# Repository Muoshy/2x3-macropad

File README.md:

# 2x3 Macropad

Extremely simple 2x3 macropad with sandwich case.

  - QMK firmware
  - Acrylic sandwich case
  - Encoder support
  
## Schematic

## PCB

## Case

Case plates for laser cutting. 0.15 mm kerf already accounted for in .dxf files.
Choose one of the three switch plates according to your encoder placement. 
For same results as image above, engrave on 2 layer acrylic.

  - 4x M3 20mm screws
  - 4x M3 nuts

## Software
Running on QMK firmware. Use QMK Toolbox to flash with provided HEX file.
Then use VIA configurator to configure keybinds.
For further customization (encoder keycodes), setup a QMK build environment and compile your own HEX files.

## Flashing
  - Download and open QMK Toolbox
  - Select HEX file
  - Choose ATMega32u4 as microcontroller
  - Push reset button on board and then press flash button in toolbox.

## Keybinds
  - Download and install VIA Configurator
  - Open VIA and go to File->Import Keymap
  - Select the keymap.json file
  - Plug in the macropad

## BOM

| Component                		| Quantity 	| Link 								|
|--------------------------		|----------	|------								|
| MX switches              		| 6x (5x)   |      								|
| 1N4148 diodes            		| 6x       	|      								|
| 5.2x5.2mm SMD pushbutton 		| 1x       	| [Mouser](https://www.google.com) 	|
| Arduino Pro Micro 5V 16 MHz   | 1x       	|      								|
| WS2812B                  		| 2x       	|      								|
| EC11 Encoder 15mm shaft   	| 1x       	|      								|

WS2812B optional as undeglow is not the best on this board due to few LEDs and bad placement.
Only 5 switches needed if also using encoder.

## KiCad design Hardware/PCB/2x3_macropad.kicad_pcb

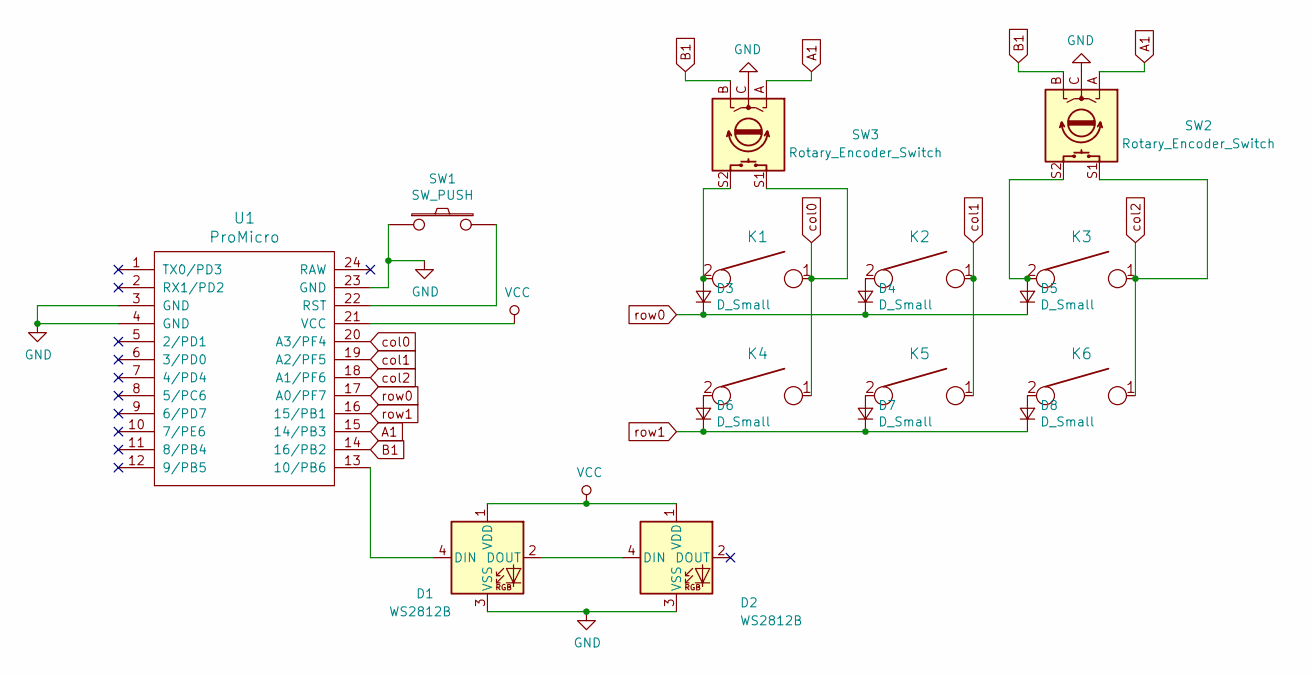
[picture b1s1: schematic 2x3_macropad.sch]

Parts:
D1, D2: WS2812B; LED_WS2812B_PLCC4_5.0x5.0mm_P3.2mm
D3, D4, D5, D6, D7, D8: D_Small; Diode-dual
K1, K2, K3, K4, K5, K6: KEYSW; MX_PCB_100H
SW1: SW_PUSH; SW_PTS525SM15SMTR2LFS
SW2, SW3: Rotary_Encoder_Switch; RotaryEncoder_Alps_EC11E-Switch_Vertical_H20mm
U1: ProMicro; ArduinoProMicro

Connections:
A1: SW2.A, SW3.A, U1.15 (14/PB3)
B1: SW2.B, SW3.B, U1.14 (16/PB2)
GND: D1.3 (VSS), D2.3 (VSS), SW1.1, SW2.C, SW3.C, U1.3 (GND), U1.4 (GND), U1.23 (GND)
unnamed: D1.2 (DOUT), D2.4 (DIN)
unnamed: D1.4 (DIN), U1.13 (10/PB6)
unnamed: D3.2 (A), K1.2, SW3.S2
unnamed: D4.2 (A), K2.2
unnamed: D5.2 (A), K3.2, SW2.S2
unnamed: D6.2 (A), K4.2
unnamed: D7.2 (A), K5.2
unnamed: D8.2 (A), K6.2
unnamed: SW1.2, U1.22 (RST)
VCC: D1.1 (VDD), D2.1 (VDD), U1.21 (VCC)
col0: K1.1, K4.1, SW3.S1, U1.20 (A3/PF4)
col1: K2.1, K5.1, U1.19 (A2/PF5)
col2: K3.1, K6.1, SW2.S1, U1.18 (A1/PF6)
row0: D3.1 (K), D4.1 (K), D5.1 (K), U1.17 (A0/PF7)
row1: D6.1 (K), D7.1 (K), D8.1 (K), U1.16 (15/PB1)

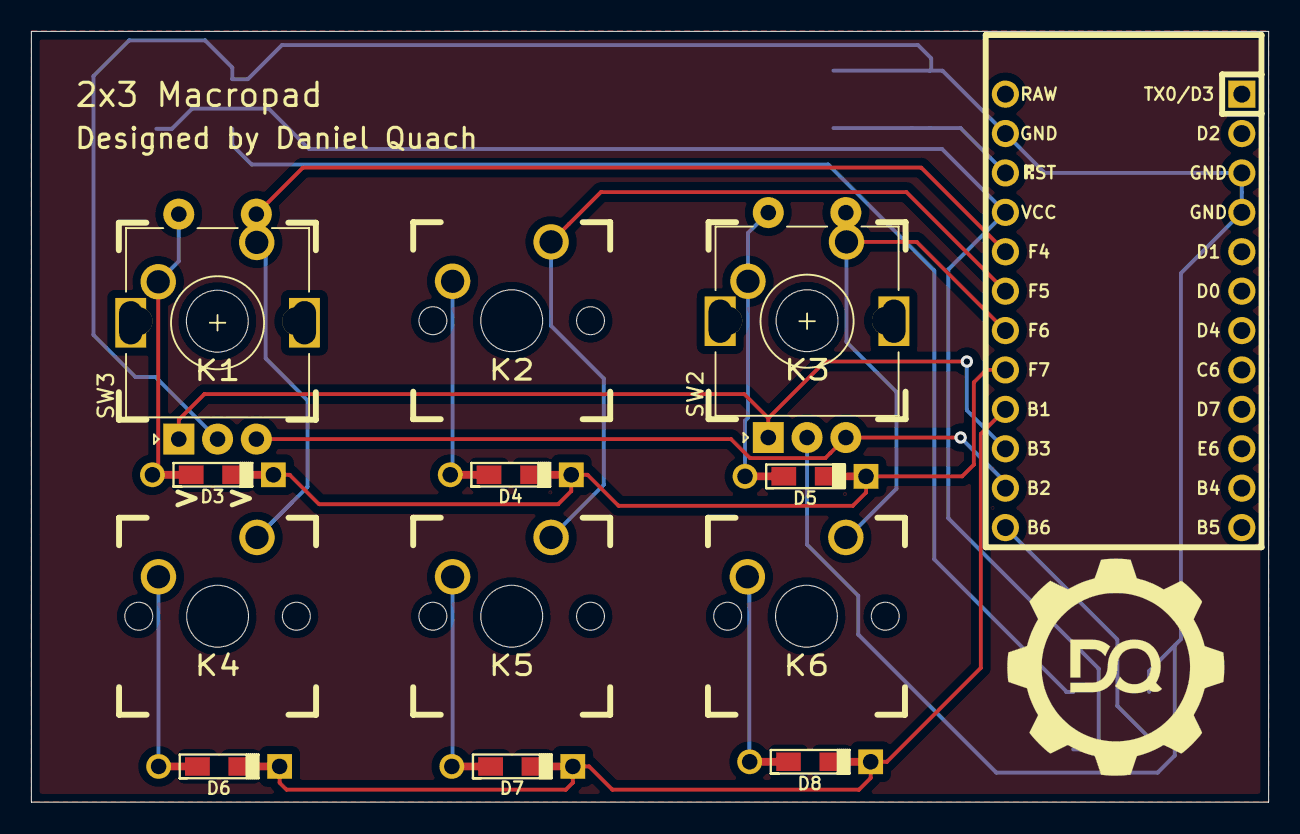
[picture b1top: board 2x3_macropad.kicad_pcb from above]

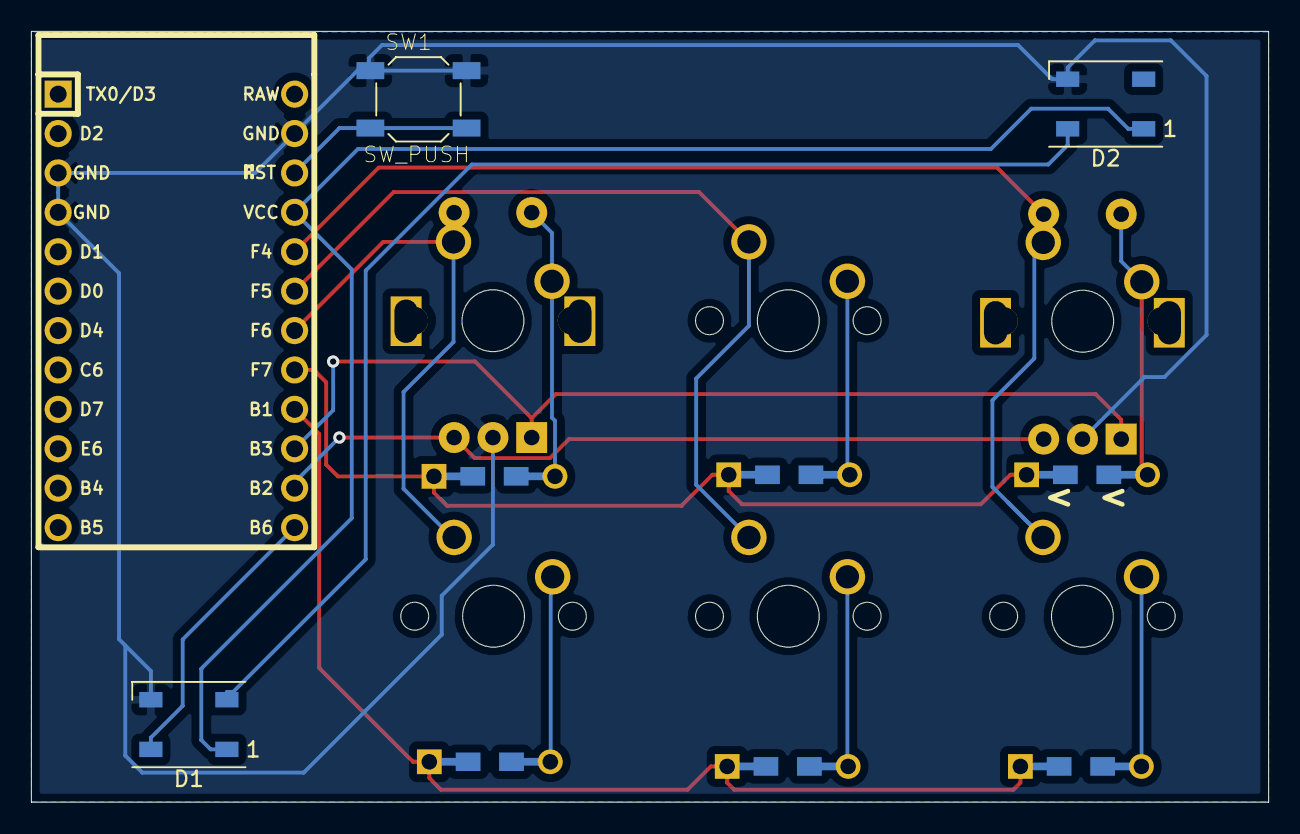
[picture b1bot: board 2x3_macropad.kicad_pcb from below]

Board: 2 copper layers, 79.8 x 49.7 mm, 18 parts (4 on the bottom side), 18 nets.

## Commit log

2020-07-23 added hardware
2020-07-25 case fixes
2020-07-25 schematic fixes
2020-07-25 renamed plate files
2020-07-25 case changes
2020-07-25 Revert "Update README.md"
    This reverts commit ee3d1fd2aba5a9bfe820731006b3502f790c9dfd.
2020-07-25 added hex and keymap
